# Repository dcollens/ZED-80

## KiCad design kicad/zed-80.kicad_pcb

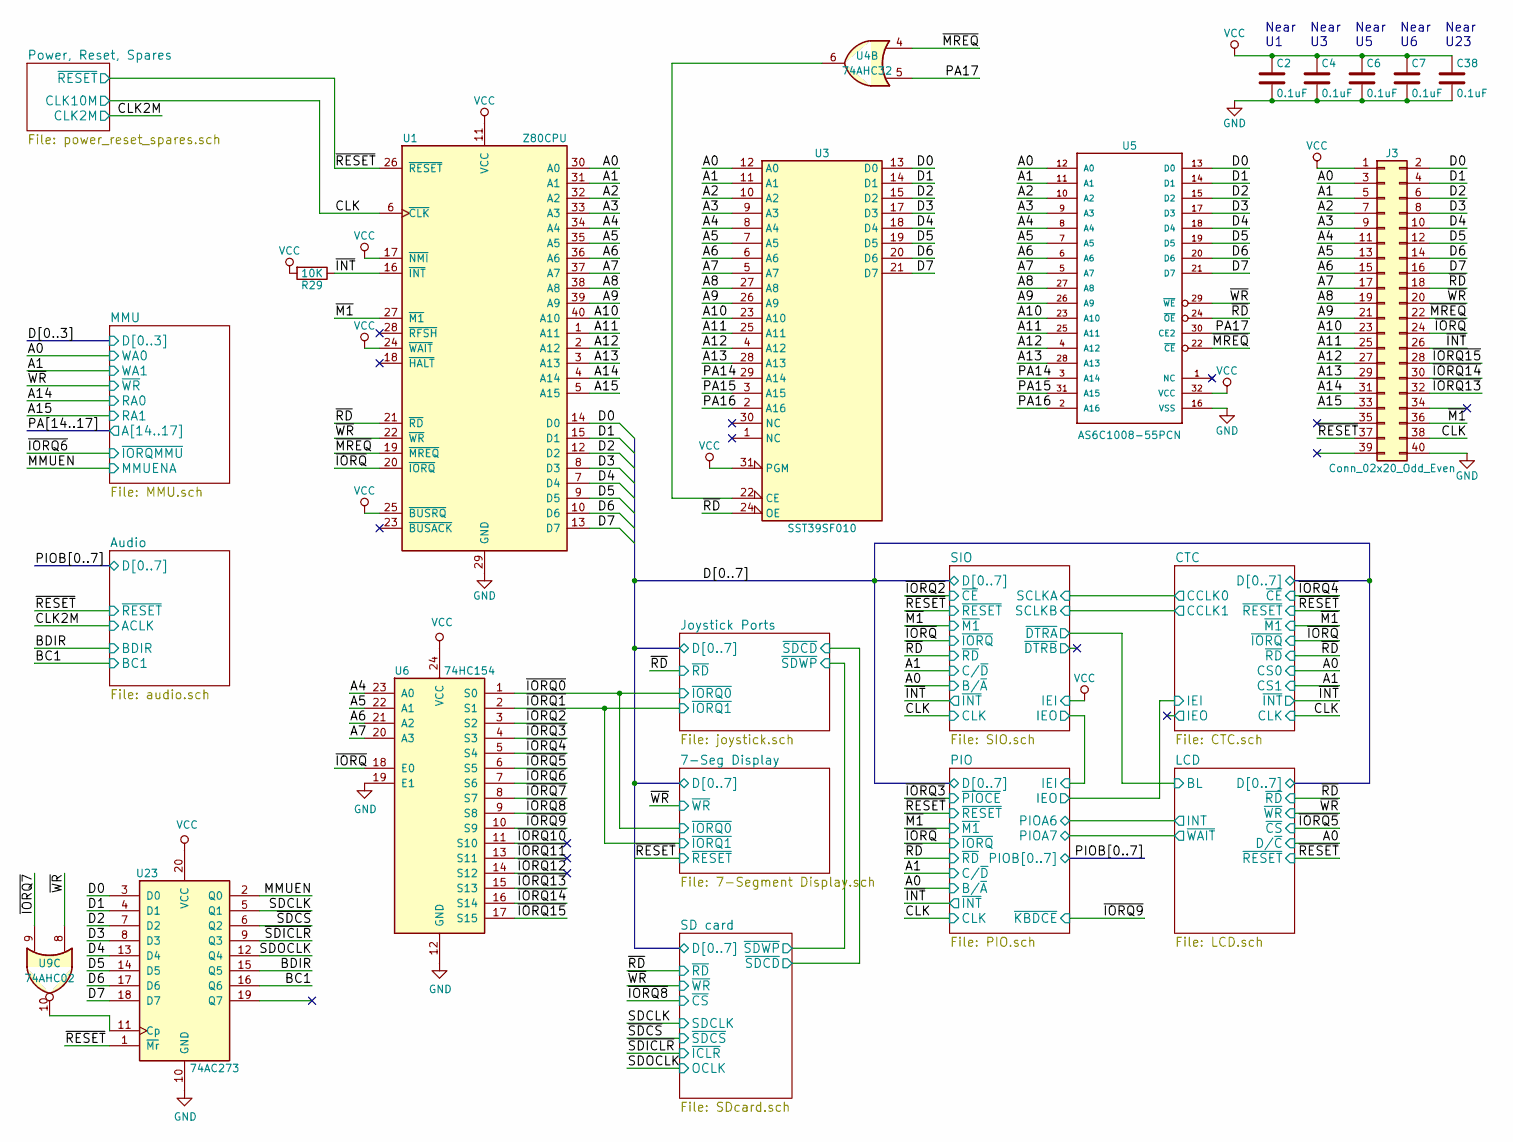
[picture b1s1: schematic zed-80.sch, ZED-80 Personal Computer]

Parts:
C2, C4, C6, C7, C38: 0.1uF; C_Disc_D4.3mm_W1.9mm_P5.00mm
J3: Conn_02x20_Odd_Even; Pin_Header_Straight_2x20_Pitch2.54mm
R29: 10K; R_0805_HandSoldering
U1: Z80CPU; DIP-40_W15.24mm_Socket
U3: SST39SF010; DIP-32_W15.24mm_Socket
U4: 74AHC32; DIP-14_W7.62mm
U5: AS6C1008-55PCN; DIP-32_W15.24mm_Socket
U6: 74HC154; SOIC-24W_7.5x15.4mm_Pitch1.27mm
U9: 74AHC02; DIP-14_W7.62mm
U23: 74AC273; TSSOP-20_4.4x6.5mm_Pitch0.65mm

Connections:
/A0: J3.3, U1.30 (A0), U3.12 (A0), U5.12 (A0); also elsewhere on the board
/A1: J3.5, U1.31 (A1), U3.11 (A1), U5.11 (A1); also elsewhere on the board
/A2: J3.7, U1.32 (A2), U3.10 (A2), U5.10 (A2)
/A3: J3.9, U1.33 (A3), U3.9 (A3), U5.9 (A3)
/A4: J3.11, U1.34 (A4), U3.8 (A4), U5.8 (A4), U6.23 (A0)
/A5: J3.13, U1.35 (A5), U3.7 (A5), U5.7 (A5), U6.22 (A1)
/A6: J3.15, U1.36 (A6), U3.6 (A6), U5.6 (A6), U6.21 (A2)
/A7: J3.17, U1.37 (A7), U3.5 (A7), U5.5 (A7), U6.20 (A3)
/A8: J3.19, U1.38 (A8), U3.27 (A8), U5.27 (A8)
/A9: J3.21, U1.39 (A9), U3.26 (A9), U5.26 (A9)
/A10: J3.23, U1.40 (A10), U3.23 (A10), U5.23 (A10)
/A11: J3.25, U1.1 (A11), U3.25 (A11), U5.25 (A11)
/A12: J3.27, U1.2 (A12), U3.4 (A12), U5.4 (A12)
/A13: J3.29, U1.3 (A13), U3.28 (A13), U5.28 (A13)
/A14: J3.31, U1.4 (A14); also elsewhere on the board
/A15: J3.33, U1.5 (A15); also elsewhere on the board
/BC1: U23.16 (Q6); also elsewhere on the board
/BDIR: U23.15 (Q5); also elsewhere on the board
/CLK: J3.38, U1.6 (~CLK~); also elsewhere on the board
/D0: J3.2, U1.14 (D0), U3.13 (D0), U5.13 (D0), U23.3 (D0); also elsewhere on the board
/D1: J3.4, U1.15 (D1), U3.14 (D1), U5.14 (D1), U23.4 (D1); also elsewhere on the board
/D2: J3.6, U1.12 (D2), U3.15 (D2), U5.15 (D2), U23.7 (D2); also elsewhere on the board
/D3: J3.8, U1.8 (D3), U3.17 (D3), U5.17 (D3), U23.8 (D3); also elsewhere on the board
/D4: J3.10, U1.7 (D4), U3.18 (D4), U5.18 (D4), U23.13 (D4); also elsewhere on the board
/D5: J3.12, U1.9 (D5), U3.19 (D5), U5.19 (D5), U23.14 (D5); also elsewhere on the board
/D6: J3.14, U1.10 (D6), U3.20 (D6), U5.20 (D6), U23.17 (D6); also elsewhere on the board
/D7: J3.16, U1.13 (D7), U3.21 (D7), U5.21 (D7), U23.18 (D7); also elsewhere on the board
/MMUEN: U23.2 (Q0); also elsewhere on the board
/PA14: U3.29 (A14), U5.3 (A14); also elsewhere on the board
/PA15: U3.3 (A15), U5.31 (A15); also elsewhere on the board
/PA16: U3.2 (A16), U5.2 (A16); also elsewhere on the board
/PA17: U4.5, U5.30 (CE2); also elsewhere on the board
/SDOCLK: U23.12 (Q4); also elsewhere on the board
/~INT: J3.26, R29.1, U1.16 (~INT~); also elsewhere on the board
/~IORQ: J3.24, U1.20 (~IORQ~), U6.18 (E0); also elsewhere on the board
/~IORQ0: U6.1 (S0); also elsewhere on the board
/~IORQ1: U6.2 (S1); also elsewhere on the board
/~IORQ2: U6.3 (S2); also elsewhere on the board
/~IORQ3: U6.4 (S3); also elsewhere on the board
/~IORQ4: U6.5 (S4); also elsewhere on the board
/~IORQ5: U6.6 (S5); also elsewhere on the board
/~IORQ6: U6.7 (S6); also elsewhere on the board
/~IORQ7: U6.8 (S7), U9.9
/~IORQ8: U6.9 (S8); also elsewhere on the board
/~IORQ9: U6.10 (S9); also elsewhere on the board
/~IORQ13: J3.32, U6.15 (S13)
/~IORQ14: J3.30, U6.16 (S14)
/~IORQ15: J3.28, U6.17 (S15)
/~M1: J3.36, U1.27 (~M1~); also elsewhere on the board
/~MREQ: J3.22, U1.19 (~MREQ~), U4.4, U5.22 (~CE)
/~RD: J3.18, U1.21 (~RD~), U3.24 (OE), U5.24 (~OE); also elsewhere on the board
/~RESET: J3.37, U1.26 (~RESET~), U23.1 (~Mr); also elsewhere on the board
/~SDICLR: U23.9 (Q3); also elsewhere on the board
/~WR: J3.20, U1.22 (~WR~), U5.29 (~WE), U9.8; also elsewhere on the board
GND: C2.2, C4.2, C6.2, C7.2, C38.2, J3.40, U1.29 (GND), U3.16 (GND), U5.16 (VSS), U6.12 (GND), U6.19 (E1), U23.10 (GND); also elsewhere on the board
unnamed: U3.22 (CE), U4.6
unnamed: U9.10, U23.11 (Cp)
SDCLK_5V: U23.5 (Q1); also elsewhere on the board
VCC: C2.1, C4.1, C6.1, C7.1, C38.1, J3.1, R29.2, U1.11 (VCC), U1.17 (~NMI~), U1.24 (~WAIT~), U1.25 (~BUSRQ~), U3.31 (PGM), U3.32 (VCC), U5.32 (VCC), U6.24 (VCC), U23.20 (VCC); also elsewhere on the board
~SDCS_5V: U23.6 (Q2); also elsewhere on the board

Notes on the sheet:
Near U1
Near U3
Near U5
Near U6
Near U23

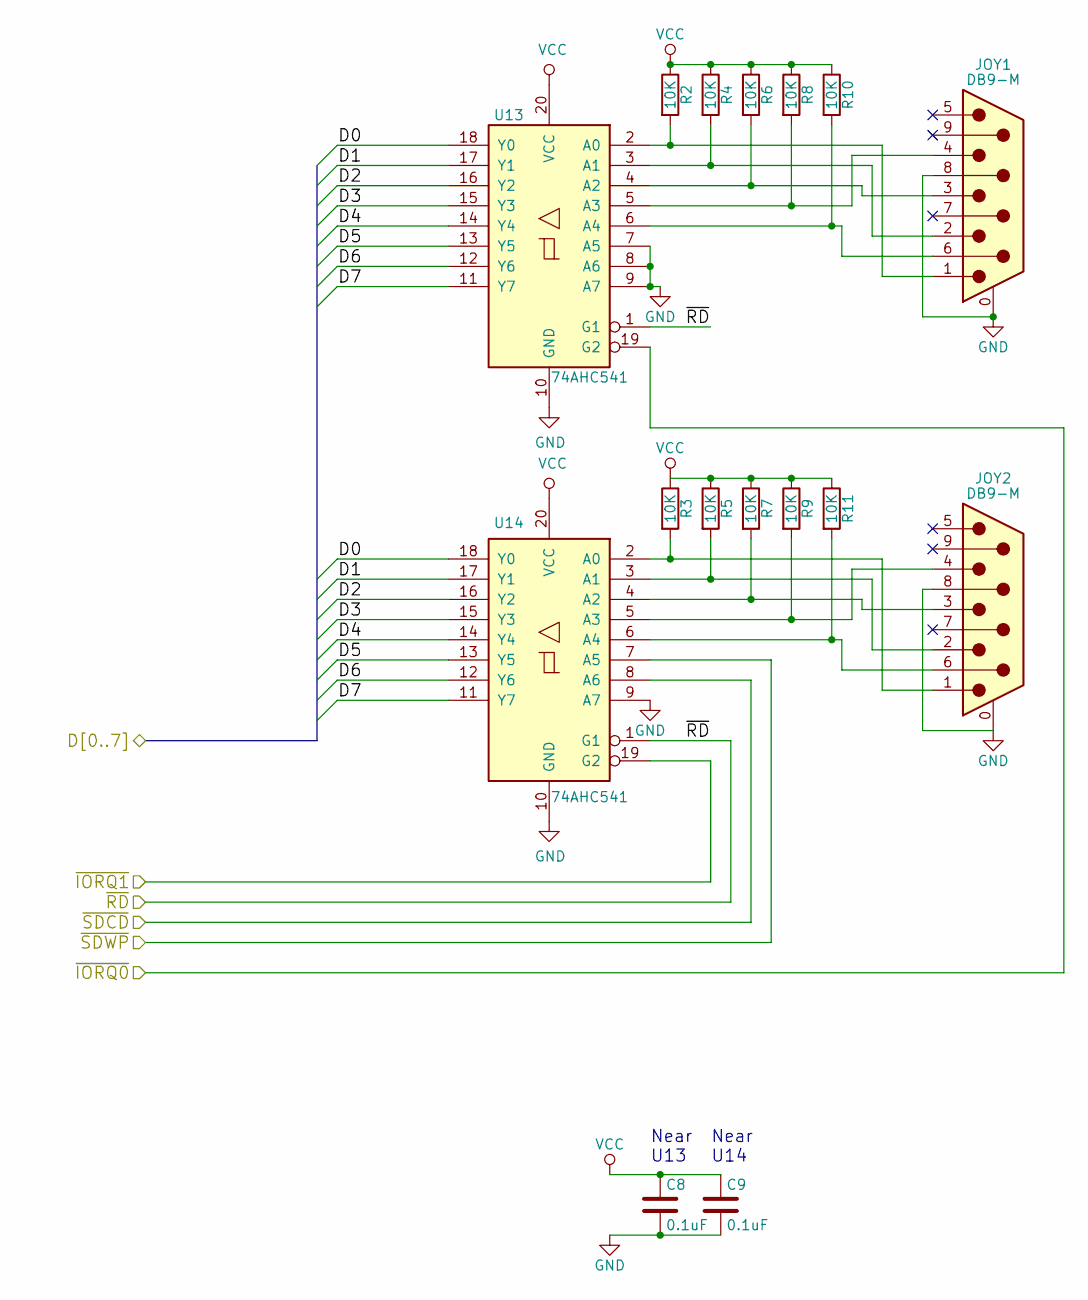
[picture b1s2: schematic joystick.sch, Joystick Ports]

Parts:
C8, C9: 0.1uF; C_Disc_D4.3mm_W1.9mm_P5.00mm
JOY1, JOY2: DB9-M; L717SDE09P1ACH
R2, R3, R4, R5, R6, R7, R8, R9, R10, R11: 10K; R_0805_HandSoldering
U13, U14: 74AHC541; TSSOP-20_4.4x6.5mm_Pitch0.65mm

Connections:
/D0: U13.18 (Y0), U14.18 (Y0); also elsewhere on the board
/D1: U13.17 (Y1), U14.17 (Y1); also elsewhere on the board
/D2: U13.16 (Y2), U14.16 (Y2); also elsewhere on the board
/D3: U13.15 (Y3), U14.15 (Y3); also elsewhere on the board
/D4: U13.14 (Y4), U14.14 (Y4); also elsewhere on the board
/D5: U13.13 (Y5), U14.13 (Y5); also elsewhere on the board
/D6: U13.12 (Y6), U14.12 (Y6); also elsewhere on the board
/D7: U13.11 (Y7), U14.11 (Y7); also elsewhere on the board
/Joystick Ports/~SDCD: U14.8 (A6); also elsewhere on the board
/Joystick Ports/~SDWP: U14.7 (A5); also elsewhere on the board
/~IORQ0: U13.19 (G2); also elsewhere on the board
/~IORQ1: U14.19 (G2); also elsewhere on the board
/~RD: U13.1 (G1), U14.1 (G1); also elsewhere on the board
GND: C8.2, C9.2, JOY1.0 (PAD), JOY1.8, JOY2.0 (PAD), JOY2.8, U13.7 (A5), U13.8 (A6), U13.9 (A7), U13.10 (GND), U14.9 (A7), U14.10 (GND); also elsewhere on the board
unnamed: JOY1.1, R2.2, U13.2 (A0)
unnamed: JOY1.2, R4.2, U13.3 (A1)
unnamed: JOY1.3, R6.2, U13.4 (A2)
unnamed: JOY1.4, R8.2, U13.5 (A3)
unnamed: JOY1.6, R10.2, U13.6 (A4)
unnamed: JOY2.1, R3.2, U14.2 (A0)
unnamed: JOY2.2, R5.2, U14.3 (A1)
unnamed: JOY2.3, R7.2, U14.4 (A2)
unnamed: JOY2.4, R9.2, U14.5 (A3)
unnamed: JOY2.6, R11.2, U14.6 (A4)
VCC: C8.1, C9.1, R2.1, R3.1, R4.1, R5.1, R6.1, R7.1, R8.1, R9.1, R10.1, R11.1, U13.20 (VCC), U14.20 (VCC); also elsewhere on the board

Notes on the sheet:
Near U13
Near U14

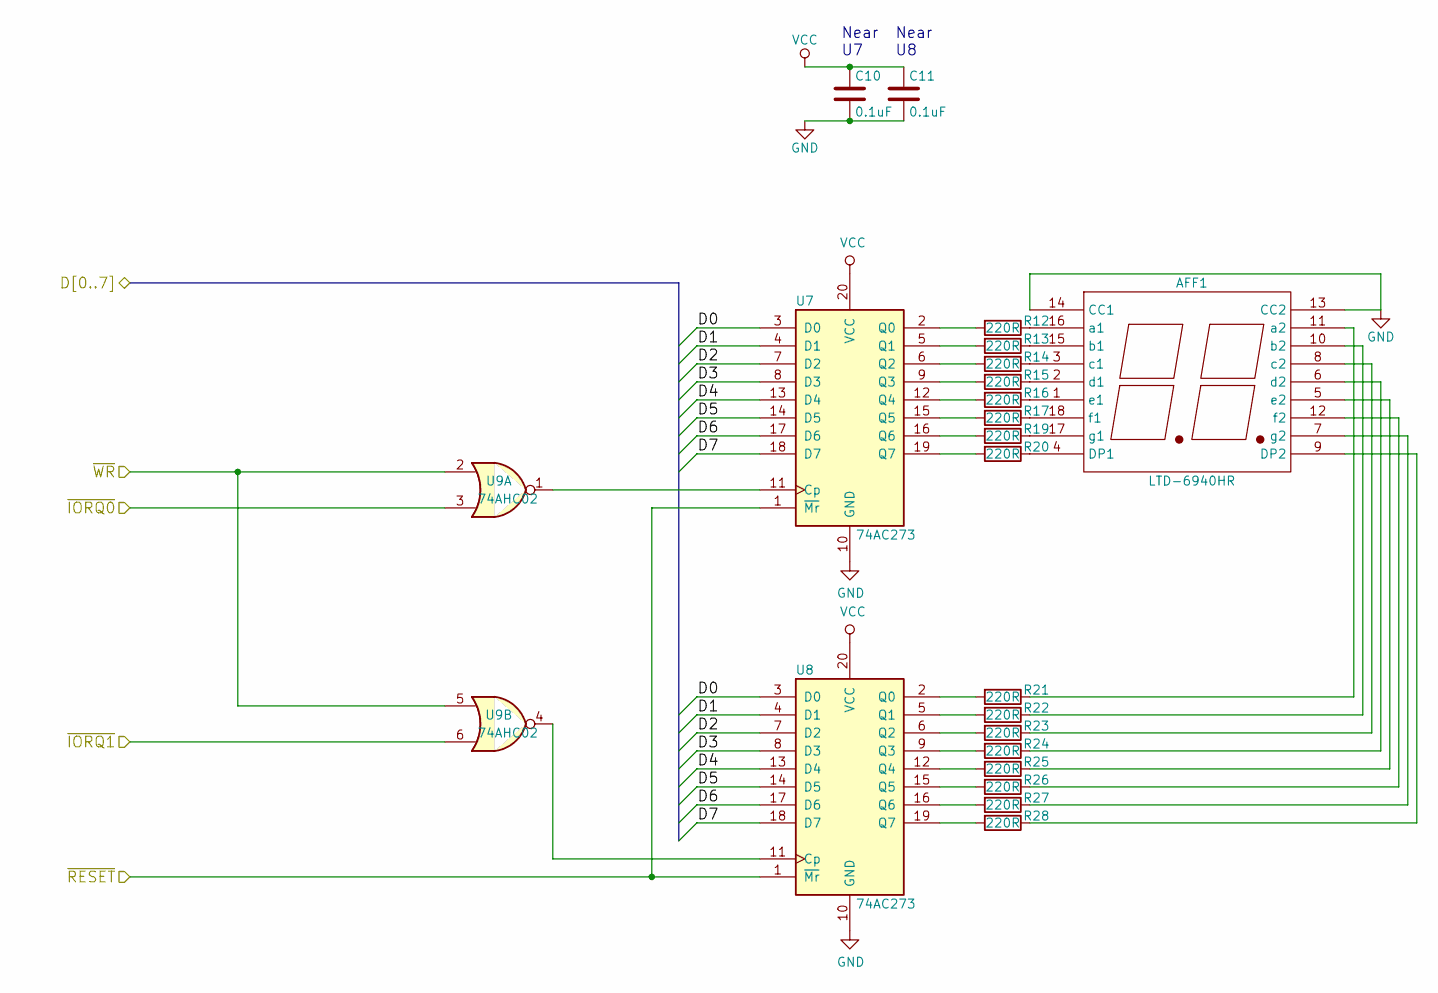
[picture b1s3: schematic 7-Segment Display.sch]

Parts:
AFF1: LTD-6940HR
C10, C11: 0.1uF; C_Disc_D4.3mm_W1.9mm_P5.00mm
R12, R13, R14, R15, R16, R17, R19, R20, R21, R22, R23, R24, R25, R26, R27, R28: 220R; R_Axial_DIN0204_L3.6mm_D1.6mm_P5.08mm_Horizontal
U7, U8: 74AC273; TSSOP-20_4.4x6.5mm_Pitch0.65mm
U9: 74AHC02; DIP-14_W7.62mm

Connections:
/D0: U7.3 (D0), U8.3 (D0); also elsewhere on the board
/D1: U7.4 (D1), U8.4 (D1); also elsewhere on the board
/D2: U7.7 (D2), U8.7 (D2); also elsewhere on the board
/D3: U7.8 (D3), U8.8 (D3); also elsewhere on the board
/D4: U7.13 (D4), U8.13 (D4); also elsewhere on the board
/D5: U7.14 (D5), U8.14 (D5); also elsewhere on the board
/D6: U7.17 (D6), U8.17 (D6); also elsewhere on the board
/D7: U7.18 (D7), U8.18 (D7); also elsewhere on the board
/~IORQ0: U9.3; also elsewhere on the board
/~IORQ1: U9.6; also elsewhere on the board
/~RESET: U7.1 (~Mr), U8.1 (~Mr); also elsewhere on the board
/~WR: U9.2, U9.5; also elsewhere on the board
GND: AFF1.13 (CC2), AFF1.14 (CC1), C10.2, C11.2, U7.10 (GND), U8.10 (GND); also elsewhere on the board
unnamed: AFF1.1 (e1), R16.1
unnamed: AFF1.2 (d1), R15.1
unnamed: AFF1.3 (c1), R14.1
unnamed: AFF1.4 (DP1), R20.1
unnamed: AFF1.5 (e2), R25.1
unnamed: AFF1.6 (d2), R24.1
unnamed: AFF1.7 (g2), R27.1
unnamed: AFF1.8 (c2), R23.1
unnamed: AFF1.9 (DP2), R28.1
unnamed: AFF1.10 (b2), R22.1
unnamed: AFF1.11 (a2), R21.1
unnamed: AFF1.12 (f2), R26.1
unnamed: AFF1.15 (b1), R13.1
unnamed: AFF1.16 (a1), R12.1
unnamed: AFF1.17 (g1), R19.1
unnamed: AFF1.18 (f1), R17.1
unnamed: R12.2, U7.2 (Q0)
unnamed: R13.2, U7.5 (Q1)
unnamed: R14.2, U7.6 (Q2)
unnamed: R15.2, U7.9 (Q3)
unnamed: R16.2, U7.12 (Q4)
unnamed: R17.2, U7.15 (Q5)
unnamed: R19.2, U7.16 (Q6)
unnamed: R20.2, U7.19 (Q7)
unnamed: R21.2, U8.2 (Q0)
unnamed: R22.2, U8.5 (Q1)
unnamed: R23.2, U8.6 (Q2)
unnamed: R24.2, U8.9 (Q3)
unnamed: R25.2, U8.12 (Q4)
unnamed: R26.2, U8.15 (Q5)
unnamed: R27.2, U8.16 (Q6)
unnamed: R28.2, U8.19 (Q7)
unnamed: U7.11 (Cp), U9.1
unnamed: U8.11 (Cp), U9.4
VCC: C10.1, C11.1, U7.20 (VCC), U8.20 (VCC); also elsewhere on the board

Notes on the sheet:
Near U7
Near U8

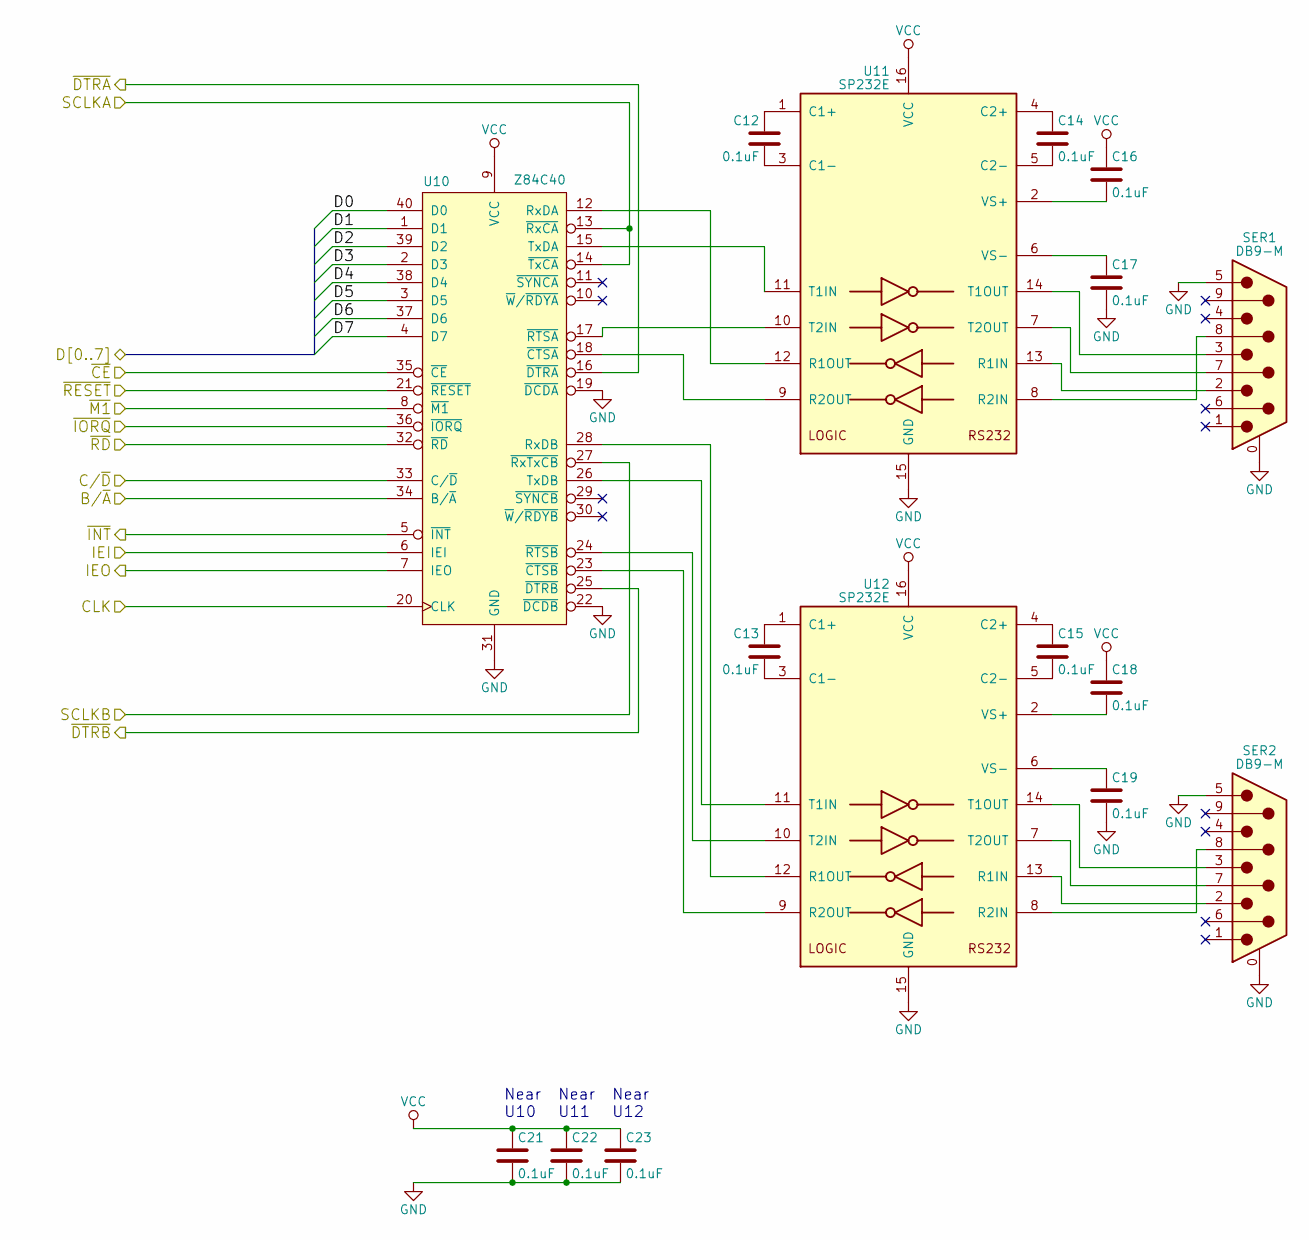
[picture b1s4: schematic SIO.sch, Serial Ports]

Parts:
C12, C13, C14, C15, C16, C17, C18, C19, C21, C22, C23: 0.1uF; C_Disc_D4.3mm_W1.9mm_P5.00mm
SER1, SER2: DB9-M; L717SDE09P1ACH
U10: Z84C40; DIP-40_W15.24mm_Socket
U11, U12: SP232E; DIP-16_W7.62mm

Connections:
/A0: U10.34 (B/~A); also elsewhere on the board
/A1: U10.33 (C/~D); also elsewhere on the board
/CLK: U10.20 (CLK); also elsewhere on the board
/CTC/CCLK0: U10.13 (~RxCA), U10.14 (~TxCA); also elsewhere on the board
/CTC/CCLK1: U10.27 (~RxTxCB); also elsewhere on the board
/D0: U10.40 (D0); also elsewhere on the board
/D1: U10.1 (D1); also elsewhere on the board
/D2: U10.39 (D2); also elsewhere on the board
/D3: U10.2 (D3); also elsewhere on the board
/D4: U10.38 (D4); also elsewhere on the board
/D5: U10.3 (D5); also elsewhere on the board
/D6: U10.37 (D6); also elsewhere on the board
/D7: U10.4 (D7); also elsewhere on the board
/LCD/BL: U10.16 (~DTRA); also elsewhere on the board
/PIO/IEI: U10.7 (IEO); also elsewhere on the board
/~INT: U10.5 (~INT); also elsewhere on the board
/~IORQ: U10.36 (~IORQ); also elsewhere on the board
/~IORQ2: U10.35 (~CE); also elsewhere on the board
/~M1: U10.8 (~M1); also elsewhere on the board
/~RD: U10.32 (~RD); also elsewhere on the board
/~RESET: U10.21 (~RESET); also elsewhere on the board
GND: C17.2, C19.2, C21.2, C22.2, C23.2, SER1.0 (PAD), SER1.5, SER2.0 (PAD), SER2.5, U10.19 (~DCDA), U10.22 (~DCDB), U10.31 (GND), U11.15 (GND), U12.15 (GND); also elsewhere on the board
unnamed: C12.1, U11.1 (C1+)
unnamed: C12.2, U11.3 (C1-)
unnamed: C13.1, U12.1 (C1+)
unnamed: C13.2, U12.3 (C1-)
unnamed: C14.1, U11.4 (C2+)
unnamed: C14.2, U11.5 (C2-)
unnamed: C15.1, U12.4 (C2+)
unnamed: C15.2, U12.5 (C2-)
unnamed: C16.2, U11.2 (VS+)
unnamed: C17.1, U11.6 (VS-)
unnamed: C18.2, U12.2 (VS+)
unnamed: C19.1, U12.6 (VS-)
unnamed: SER1.2, U11.13 (R1IN)
unnamed: SER1.3, U11.14 (T1OUT)
unnamed: SER1.7, U11.7 (T2OUT)
unnamed: SER1.8, U11.8 (R2IN)
unnamed: SER2.2, U12.13 (R1IN)
unnamed: SER2.3, U12.14 (T1OUT)
unnamed: SER2.7, U12.7 (T2OUT)
unnamed: SER2.8, U12.8 (R2IN)
unnamed: U10.12 (RxDA), U11.12 (R1OUT)
unnamed: U10.15 (TxDA), U11.11 (T1IN)
unnamed: U10.17 (~RTSA), U11.10 (T2IN)
unnamed: U10.18 (~CTSA), U11.9 (R2OUT)
unnamed: U10.23 (~CTSB), U12.9 (R2OUT)
unnamed: U10.24 (~RTSB), U12.10 (T2IN)
unnamed: U10.26 (TxDB), U12.11 (T1IN)
unnamed: U10.28 (RxDB), U12.12 (R1OUT)
VCC: C16.1, C18.1, C21.1, C22.1, C23.1, U10.6 (IEI), U10.9 (VCC), U11.16 (VCC), U12.16 (VCC); also elsewhere on the board

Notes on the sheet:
Near U10
Near U11
Near U12

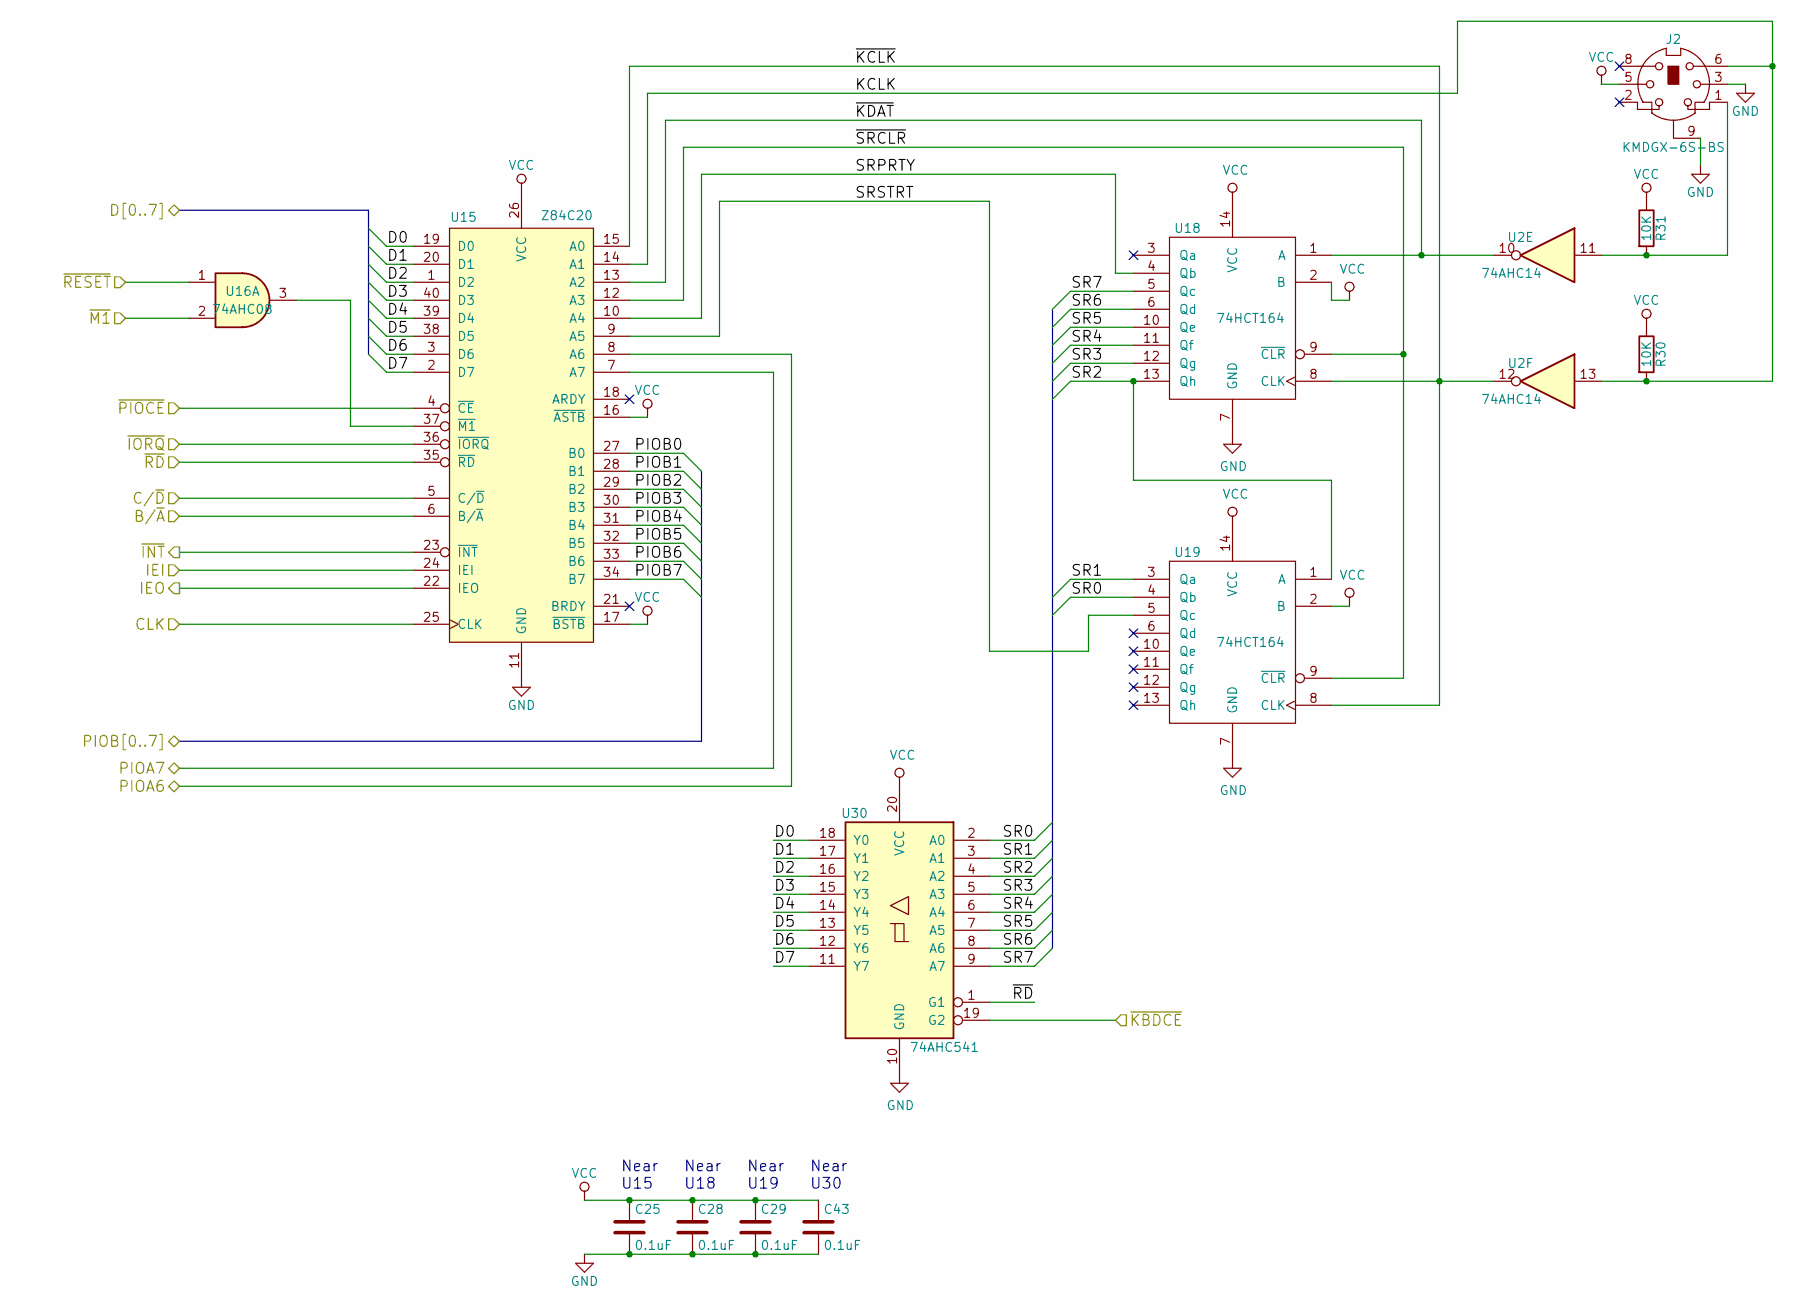
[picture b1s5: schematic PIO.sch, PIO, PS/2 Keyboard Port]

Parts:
C25, C28, C29, C43: 0.1uF; C_Disc_D4.3mm_W1.9mm_P5.00mm
J2: KMDGX-6S-BS
R30, R31: 10K; R_0805_HandSoldering
U2: 74AHC14; DIP-14_W7.62mm
U15: Z84C20; DIP-40_W15.24mm_Socket
U16: 74AHC08; DIP-14_W7.62mm
U18, U19: 74HCT164; TSSOP-14_4.4x5mm_Pitch0.65mm
U30: 74AHC541; TSSOP-20_4.4x6.5mm_Pitch0.65mm

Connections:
/A0: U15.6 (B/~A); also elsewhere on the board
/A1: U15.5 (C/~D); also elsewhere on the board
/Audio/D0: U15.27 (B0); also elsewhere on the board
/Audio/D1: U15.28 (B1); also elsewhere on the board
/Audio/D2: U15.29 (B2); also elsewhere on the board
/Audio/D3: U15.30 (B3); also elsewhere on the board
/Audio/D4: U15.31 (B4); also elsewhere on the board
/Audio/D5: U15.32 (B5); also elsewhere on the board
/Audio/D6: U15.33 (B6); also elsewhere on the board
/Audio/D7: U15.34 (B7); also elsewhere on the board
/CLK: U15.25 (CLK); also elsewhere on the board
/CTC/IEI: U15.22 (IEO); also elsewhere on the board
/D0: U15.19 (D0), U30.18 (Y0); also elsewhere on the board
/D1: U15.20 (D1), U30.17 (Y1); also elsewhere on the board
/D2: U15.1 (D2), U30.16 (Y2); also elsewhere on the board
/D3: U15.40 (D3), U30.15 (Y3); also elsewhere on the board
/D4: U15.39 (D4), U30.14 (Y4); also elsewhere on the board
/D5: U15.38 (D5), U30.13 (Y5); also elsewhere on the board
/D6: U15.3 (D6), U30.12 (Y6); also elsewhere on the board
/D7: U15.2 (D7), U30.11 (Y7); also elsewhere on the board
/LCD/INT: U15.8 (A6); also elsewhere on the board
/PIO/IEI: U15.24 (IEI); also elsewhere on the board
/PIO/KCLK: J2.6, R30.2, U2.13, U15.14 (A1)
/PIO/PIOA7: U15.7 (A7); also elsewhere on the board
/PIO/SR0: U19.4 (Qb), U30.2 (A0)
/PIO/SR1: U19.3 (Qa), U30.3 (A1)
/PIO/SR2: U18.13 (Qh), U19.1 (A), U30.4 (A2)
/PIO/SR3: U18.12 (Qg), U30.5 (A3)
/PIO/SR4: U18.11 (Qf), U30.6 (A4)
/PIO/SR5: U18.10 (Qe), U30.7 (A5)
/PIO/SR6: U18.6 (Qd), U30.8 (A6)
/PIO/SR7: U18.5 (Qc), U30.9 (A7)
/PIO/SRPRTY: U15.10 (A4), U18.4 (Qb)
/PIO/SRSTRT: U15.9 (A5), U19.5 (Qc)
/PIO/~KCLK: U2.12, U15.15 (A0), U18.8 (CLK), U19.8 (CLK)
/PIO/~KDAT: U2.10, U15.13 (A2), U18.1 (A)
/PIO/~SRCLR: U15.12 (A3), U18.9 (~CLR), U19.9 (~CLR)
/~INT: U15.23 (~INT); also elsewhere on the board
/~IORQ: U15.36 (~IORQ); also elsewhere on the board
/~IORQ3: U15.4 (~CE); also elsewhere on the board
/~IORQ9: U30.19 (G2); also elsewhere on the board
/~M1: U16.2; also elsewhere on the board
/~RD: U15.35 (~RD), U30.1 (G1); also elsewhere on the board
/~RESET: U16.1; also elsewhere on the board
GND: C25.2, C28.2, C29.2, C43.2, J2.3, J2.9, U15.11 (GND), U18.7 (GND), U19.7 (GND), U30.10 (GND); also elsewhere on the board
unnamed: J2.1, R31.2, U2.11
unnamed: U15.37 (~M1), U16.3
VCC: C25.1, C28.1, C29.1, C43.1, J2.5, R30.1, R31.1, U15.16 (~ASTB), U15.17 (~BSTB), U15.26 (VCC), U18.2 (B), U18.14 (VCC), U19.2 (B), U19.14 (VCC), U30.20 (VCC); also elsewhere on the board

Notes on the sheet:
Near U15
Near U18
Near U19
Near U30

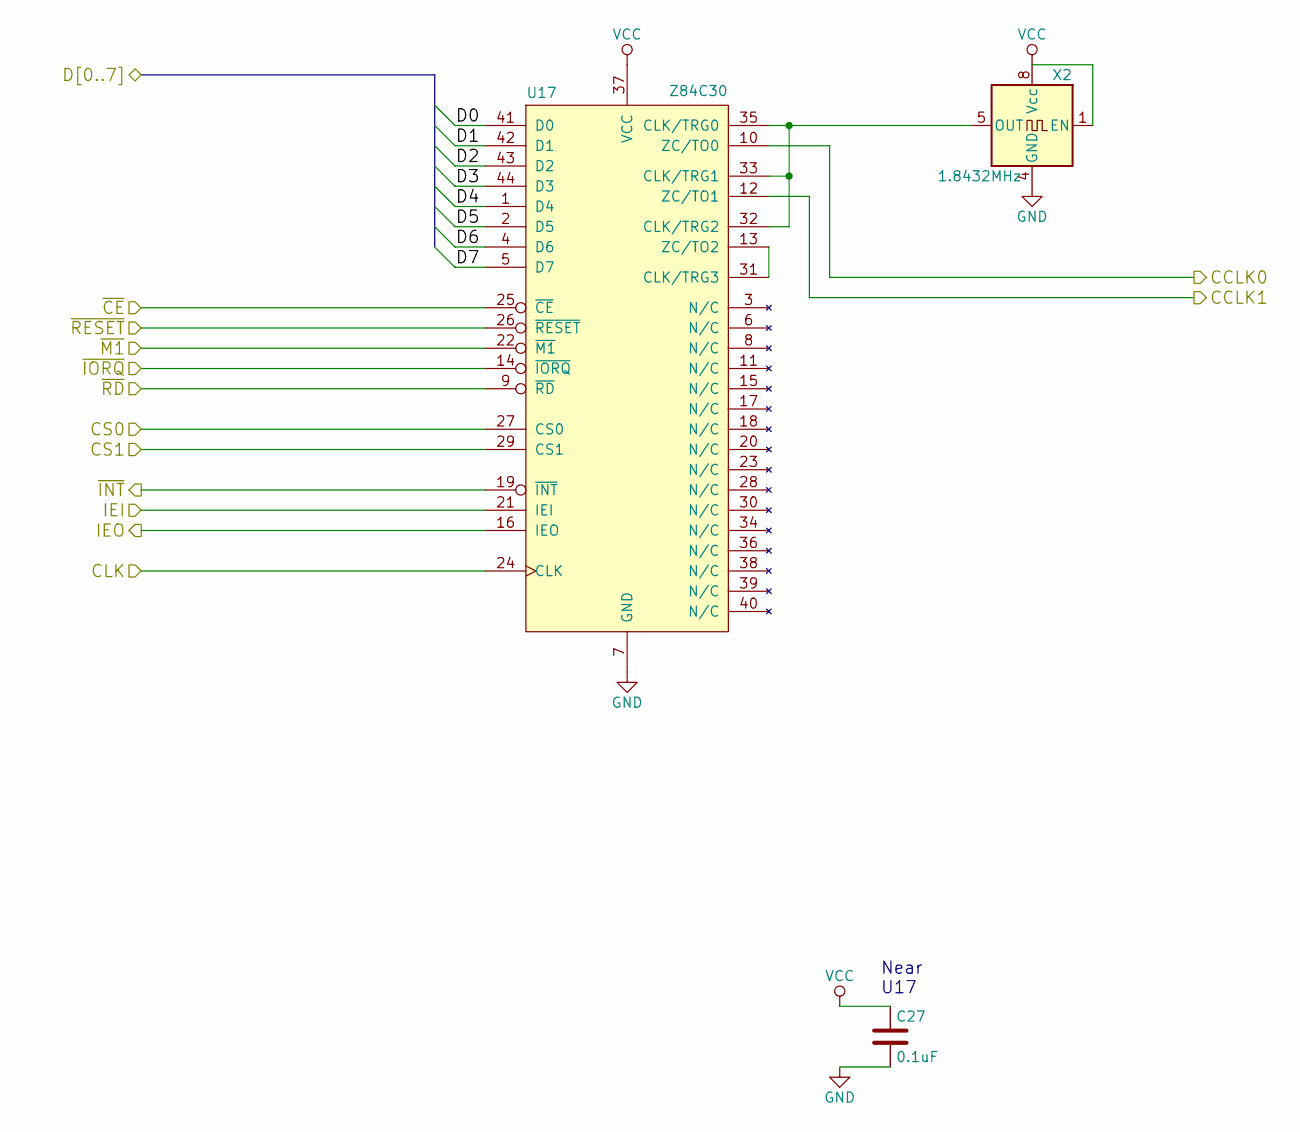
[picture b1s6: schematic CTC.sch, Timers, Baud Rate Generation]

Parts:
C27: 0.1uF; C_Disc_D4.3mm_W1.9mm_P5.00mm
U17: Z84C30; 8444-11B1-RK-TP
X2: 1.8432MHz; Oscillator_DIP-8

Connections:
/A0: U17.27 (CS0); also elsewhere on the board
/A1: U17.29 (CS1); also elsewhere on the board
/CLK: U17.24 (CLK); also elsewhere on the board
/CTC/CCLK0: U17.10 (ZC/TO0); also elsewhere on the board
/CTC/CCLK1: U17.12 (ZC/TO1); also elsewhere on the board
/CTC/IEI: U17.21 (IEI); also elsewhere on the board
/D0: U17.41 (D0); also elsewhere on the board
/D1: U17.42 (D1); also elsewhere on the board
/D2: U17.43 (D2); also elsewhere on the board
/D3: U17.44 (D3); also elsewhere on the board
/D4: U17.1 (D4); also elsewhere on the board
/D5: U17.2 (D5); also elsewhere on the board
/D6: U17.4 (D6); also elsewhere on the board
/D7: U17.5 (D7); also elsewhere on the board
/~INT: U17.19 (~INT); also elsewhere on the board
/~IORQ: U17.14 (~IORQ); also elsewhere on the board
/~IORQ4: U17.25 (~CE); also elsewhere on the board
/~M1: U17.22 (~M1); also elsewhere on the board
/~RD: U17.9 (~RD); also elsewhere on the board
/~RESET: U17.26 (~RESET); also elsewhere on the board
GND: C27.2, U17.7 (GND), X2.4 (GND); also elsewhere on the board
unnamed: U17.13 (ZC/TO2), U17.31 (CLK/TRG3)
unnamed: U17.32 (CLK/TRG2), U17.33 (CLK/TRG1), U17.35 (CLK/TRG0), X2.5 (OUT)
VCC: C27.1, U17.37 (VCC), X2.1 (EN), X2.8 (Vcc); also elsewhere on the board

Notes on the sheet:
Near U17

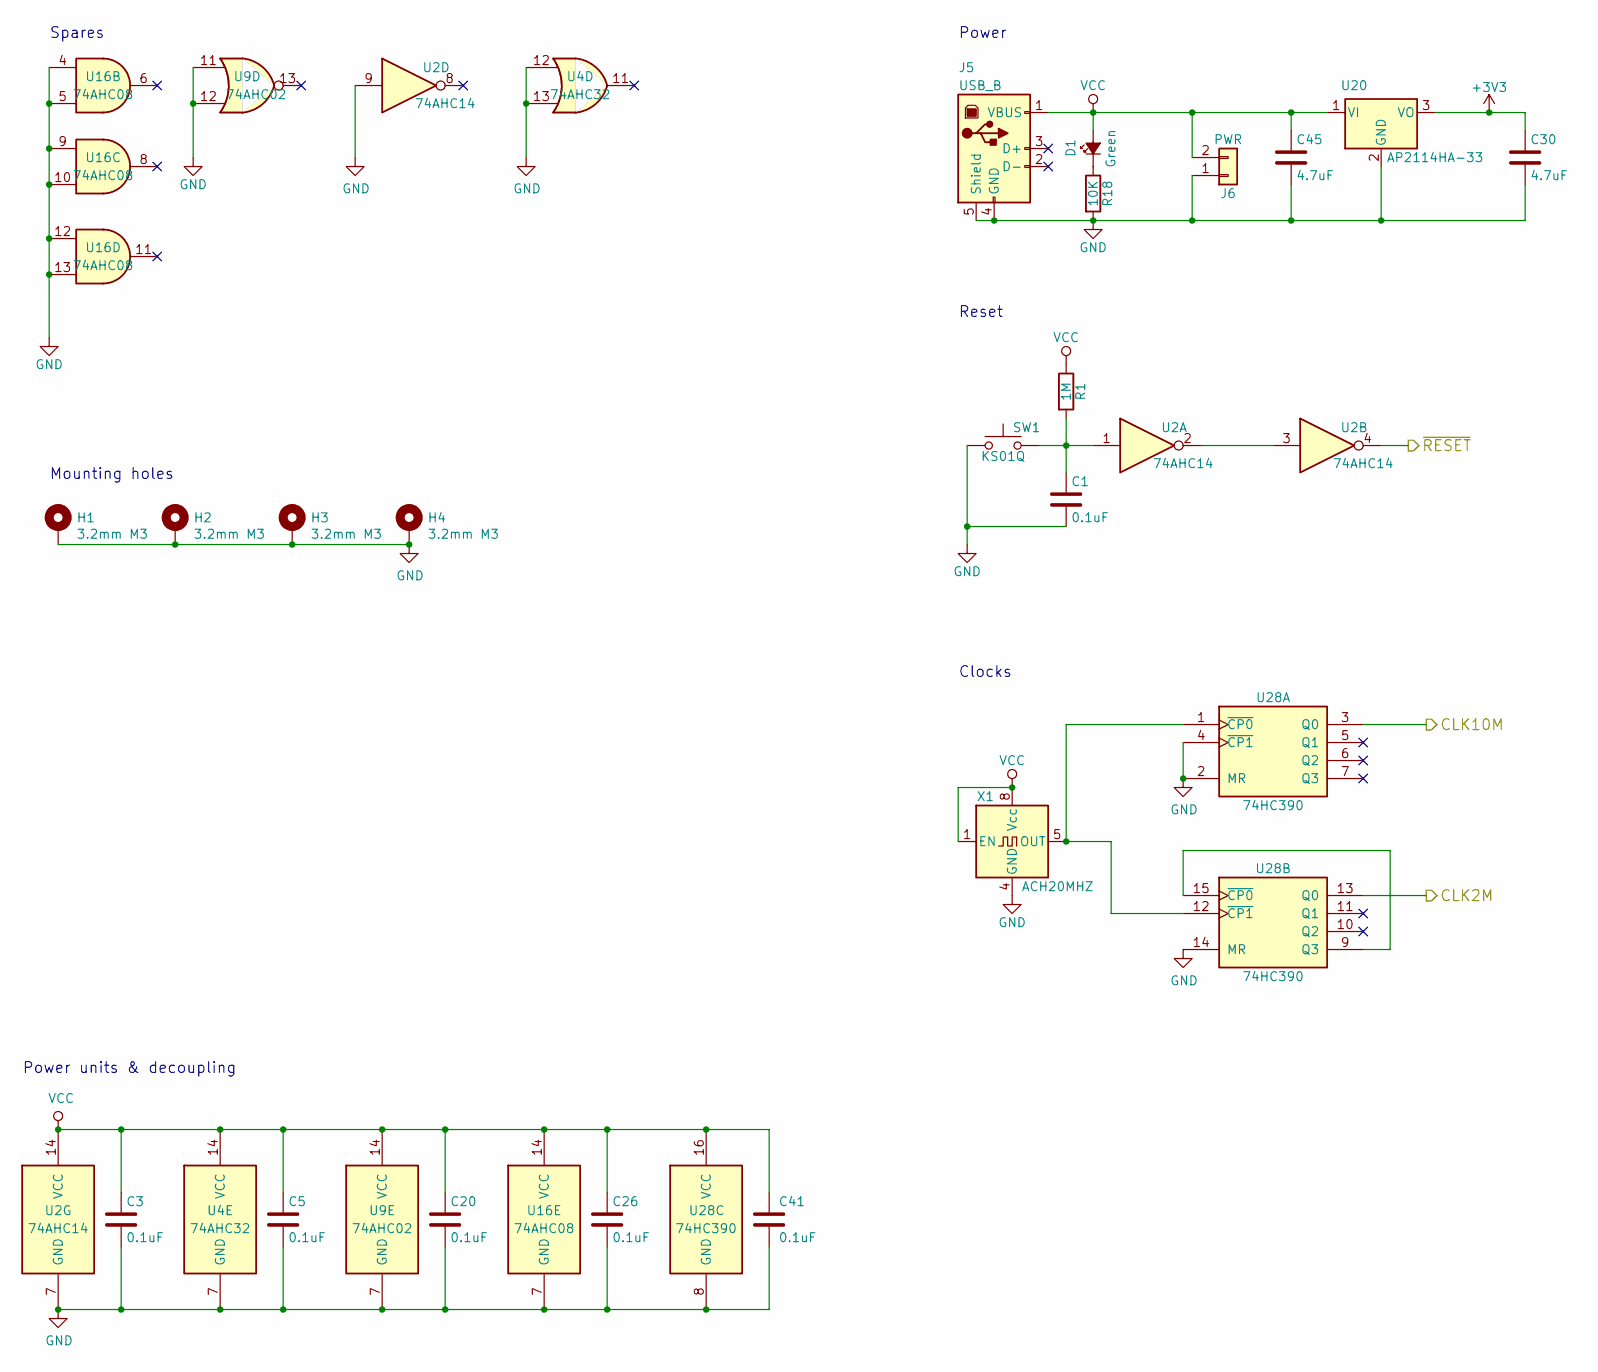
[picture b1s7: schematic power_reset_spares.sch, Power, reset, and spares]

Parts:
C1, C3, C5, C20, C26, C41: 0.1uF; C_Disc_D4.3mm_W1.9mm_P5.00mm
C30, C45: 4.7uF; C_0805_HandSoldering
D1: Green; LED_D5.0mm
H1, H2, H3, H4: 3.2mm M3; MountingHole_3.2mm_M3_Pad
J5: USB_B; USB_B_E8144-B02022-L
J6: PWR; Pin_Header_Straight_2x01_Pitch2.54mm
R1: 1M; R_Axial_DIN0204_L3.6mm_D1.6mm_P5.08mm_Horizontal
R18: 10K; R_0805_HandSoldering
SW1: KS01Q; KS-01Q-02
U2: 74AHC14; DIP-14_W7.62mm
U4: 74AHC32; DIP-14_W7.62mm
U9: 74AHC02; DIP-14_W7.62mm
U16: 74AHC08; DIP-14_W7.62mm
U20: AP2114HA-33; SOT-223-3_TabPin2
U28: 74HC390; TSSOP-16_4.4x5mm_Pitch0.65mm
X1: ACH20MHZ; Oscillator_DIP-8

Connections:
+3V3: C30.1, U20.3 (VO); also elsewhere on the board
/CLK: U28.3 (Q0); also elsewhere on the board
/CLK2M: U28.13 (Q0); also elsewhere on the board
/~RESET: U2.4; also elsewhere on the board
GND: C1.2, C3.2, C5.2, C20.2, C26.2, C30.2, C41.2, C45.2, H1.1, H2.1, H3.1, H4.1, J5.4 (GND), J5.5 (Shield), J6.1, R18.2, SW1.1, U2.7 (GND), U2.9, U4.7 (GND), U4.12, U4.13, U9.7 (GND), U9.11, U9.12, U16.4, U16.5, U16.7 (GND), U16.9, U16.10, U16.12, U16.13, U20.2 (GND), U28.2 (MR), U28.4 (~CP1), U28.8 (GND), U28.14 (MR), X1.4 (GND); also elsewhere on the board
unnamed: C1.1, R1.2, SW1.2, U2.1
unnamed: D1.1 (K), R18.1
unnamed: U2.2, U2.3
unnamed: U28.1 (~CP0), U28.12 (~CP1), X1.5 (OUT)
unnamed: U28.9 (Q3), U28.15 (~CP0)
VCC: C3.1, C5.1, C20.1, C26.1, C41.1, C45.1, D1.2 (A), J5.1 (VBUS), J6.2, R1.1, U2.14 (VCC), U4.14 (VCC), U9.14 (VCC), U16.14 (VCC), U20.1 (VI), U28.16 (VCC), X1.1 (EN), X1.8 (Vcc); also elsewhere on the board

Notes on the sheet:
Spares
Power units & decoupling
Power
Reset
Clocks
Mounting holes
